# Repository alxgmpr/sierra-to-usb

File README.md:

# Sierra / Quectel 2.5GbE PoE modem appliance

Multi-gigabit WAN design study for **EM9190, EM9293, RM520N-GL and
RM551E-GL**. No CM4/CM5. **RK3566 is the selected Linux packet-processor
candidate for evaluation**, with an independent STM32 recovery MCU. The exact
modem tuples and complete appliance remain unqualified. The complete engineering
capture is in [hardware/appliance.kicad_pro](hardware/appliance.kicad_pro).

**Feasibility gate remains open.** Manufacturer documentation establishes Sierra
PCIe endpoint/USB-device operation, not modem-hosted Ethernet. A switch does not
supply the missing host and drivers. Quectel offload is a candidate requiring
exact firmware and NIC qualification. No modem combination is qualified.

- [Requirements and confirmed decisions](REQUIREMENTS.md)
- [Architecture, manufacturer evidence, networking and recovery](docs/architecture.md)
- [Historical MCU-only packet-path comparison](docs/packet-path.svg)
- [RK3566 processor qualification and current block diagram](docs/rockchip-qualification.md)
- [Block diagram and BOM qualification status](docs/qualification-status.md)
- [Power and complete-cost estimates](docs/power-and-cost.md)
- [Decoupling review and capacitor consolidation](docs/decoupling-review.md)
- [PoE stage: TPS23730 / PMP22477 evaluation (adopted)](docs/poe-tps23730-evaluation.md)
- [Reopened Rockchip Linux comparison and sourcing](docs/rockchip-options.md)
- [Actual KiCad recovery schematic](hardware/recovery.kicad_sch)
- [Implemented circuit, checks and outstanding qualification](hardware/README.md)

The full [33-sheet appliance schematic](hardware/appliance.kicad_sch) now captures
processor/RAM/eMMC, all supplies, 2.5GbE, isolated PoE, modem/SIM and recovery
interfaces: 818 components, 856 nets, **zero full ERC violations**.
[Review PDF](hardware/review/2026-10-07/appliance.pdf) and
[completion / release holds](docs/schematic-completion.md) are available.
All 818 PCB footprints are assigned, including 521 stock hand-solder variants.
Current CLI schematic/PCB parity is clean. October 7 native update-dialog
results are retained in the [footprint and model audit](docs/footprint-audit.md). Two BGA land-pattern/process
reviews, remaining model holds, current modem guides and physical/software
qualification remain open. Placement, routing and manufacturing release remain
pending.

The [October 21 BGA/model follow-up](docs/bga-model-review-2026-10-21.md)
adds six package-envelope models for 16 components (54 attached STEP assets total).
Eighteen missing-model holds and both BGA assembly-process holds remain explicit.

Previous designs remain only in Git history; none were restored for this work.

## Full schematic work — 2026-10-07

Complete appliance capture is saved in the canonical `hardware/appliance` project,
including the independent always-on supply and full recovery hierarchy. See
[completion evidence and release holds](docs/schematic-completion.md).

## Footprint and modem review — 2026-10-21

[Six-footprint review](docs/footprint-review-2026-10-21.md) closes four drawing
geometry holds and fixes TPS56837 paste/mask geometry and BGA grid rounding.
The two BGA PCB land/process holds remain. [Modem documentation gates](docs/modem-documentation.md)
record current download blockers and a PCIe-only RM520N order-code exclusion.
All four modem profiles remain unreleased. Full ERC and native parity still pass.

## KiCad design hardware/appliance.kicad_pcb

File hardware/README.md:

# Appliance schematic

The complete engineering capture is [appliance.kicad_sch](appliance.kicad_sch), with
33 sheets, 818 components and 856 native nets. Open [appliance.kicad_pro](appliance.kicad_pro)
in KiCad. [appliance.kicad_pcb](appliance.kicad_pcb) contains all 818 footprints
with native schematic links; placement and routing are still pending.

The remaining processor, boot storage, CPU power, Ethernet, isolated PoE,
modem power, M.2, SIM and USB isolation circuits are now captured. The engineering
capture passes full ERC at all severities, with **zero violations and no exclusions**.
Current CLI schematic/PCB parity is clean. The October 7 bidirectional native
update-dialog checks reported zero errors/warnings and no proposed changes. This is not a manufacturing or four-modem release.

[Review PDF](review/2026-10-07/appliance.pdf) ·
[Native BOM inventory](review/2026-10-07/bom.csv) ·
[Validation report](review/2026-10-07/capture-report.json) ·
[Footprint and model audit](../docs/footprint-audit.md) ·
[Detailed completion and release holds](../docs/schematic-completion.md)

## Reproduce and inspect

Requires KiCad CLI 10.99 (the version used for native Altium reference import) and
Python 3. Run without `python -O`; the checker uses assertions.

```sh
python3 hardware/check.py --output /tmp/sierra-appliance-check
python3 hardware/tools/check_board_sync.py --output /tmp/sierra-board-check
python3 hardware/tools/review_modem_power.py --output /tmp/modem-power-analysis.json
python3 hardware/tools/export_appliance.py --output /tmp/sierra-appliance-review
```

The checker validates the native netlist and all-severity ERC; all 565 RK3566,
200 RAM, 153 eMMC and other major-device contacts are accounted for. It checks
65 manufacturer DDR pair mappings, the complete retained TI bridge/flyback net
partitions, critical rail/reset/interface connections, four assembly-profile power
maps, deterministic identities and exact pad-number parity for all 818 assigned
footprints. Pad parity establishes identity, not a fabrication land-pattern review.
791 components use default KiCad footprints, including 521 stock hand-solder
variants. Existing package sizes are retained. All attached model paths resolve;
missing or mechanically unverified models are explicitly recorded in
[footprint-policy.json](footprint-policy.json). Imported TI embedded STEP assets
are now stored in the project.

The [BGA/model follow-up](../docs/bga-model-review-2026-10-21.md) records six new
package-envelope models covering 16 components, all 18 remaining missing-model
holds, and measured mask/stencil limits for the two unreleased BGAs. The full
checker validates model source hashes, attachment rotations and these holds;
`tools/check_model_reviews.py --geometry` additionally checks the six STEP solids
and sourced bounds with CadQuery.

The [2026-11-21 model follow-up](reference/model-reviews-2026-11-21.json) closes 11
more holds with `tools/build_models.py`: the archived Amphenol M.2 STEP attached
with a measured datum transform, the TI-embedded PowerDI-5 STEP re-oriented to its
lands, and nine envelopes (nominal XY, maximum height, drawing terminals) for U1301,
U701, U2002, U1902, U1901, U1001, L401, Y1101 and U1101. Every envelope terminal is
cross-checked against its footprint copper. Remaining holds stay in the policy.
Every generated model is a single flat, coloured STEP product with its datum transform
baked in and attaches with a zero transform, so KiCad and Backplane's 3D tab agree.

Use the native Update PCB / Update Schematic dialogs for normal edits, with
reference relinking off. `build_capture.py` regenerates the original capture and
applies the footprint policy; it overwrites manual schematic graphics. Preserve
editor changes before regeneration. `sync_board.py` is only an unrouted-board
refresh helper and refuses routed boards.

The PDF was rendered and all 30 sheets inspected. Cropped modem content, a duplicate
crystal-ground wire and the recovery USB shell-pad model were corrected during review.

## Bring-up additions — 2026-11-22

Four sheets from [tools/build_management.py](tools/build_management.py), plus native label edits on the
supervisor, processor, modem-socket, flyback, PMIC and 3.3 V sheets:

- **SoC <-> STM32 UART.** RK3566 UART3_M0 (A22 RX, B22 TX, VCCIO1 = 3V3_MAIN) to STM32 LPUART2
  (PC7 RX, PC6 TX) through two LVC1G125 buffers, each powered by its receiving side so neither
  back-powers the other. Carries telemetry, LED overrides, power-cycle requests and reset cause.
- **Status LEDs.** PWR/SYS/WAN (green) and FAULT (yellow) sink into STM32 PA8/PA15/PD0/PD1, all
  timer-PWM pins. They are dark from MCU reset until firmware drives them; Linux overrides over the UART.
- **Sensing on the STM32 ADC.** To free seven ADC inputs, seven digital signals moved to spare GPIOs
  ([assignment table](pinmaps/supervisor-appliance-assignment.csv)). PA0 AUX_12V/11, PA1 5V_MAIN/2,
  PA4 3V3_MAIN/2, PA5 MODEM_VCC/2, PA6 modem current from the TPS25947 ILM pin (R2213 must sit at U1902
  pin 9: the pin tolerates < 50 pF), PA7/PB2 10k NTCs at the M.2 bay and the flyback secondary.
  INA226 (I2C1 PB8/PB9, 0x40, alert on PC14) measures the whole 12 V bus through a 10 mOhm shunt.
- **Aux 12 V input.** J2101 (ED555) feeds ISO_12V_BUS through an LM74700 + CSD17577Q5A ideal diode; the
  flyback output (now `ISO_12V_PSU`) gets its own. `ISO_12V` is the monitored bus after the shunt.
  **Firmware:** aux power gives no PoE grant (TPH_N/TPL_N/BT_N all high). Bypass the grant gate only while
  ADC_AUX_12V reads above 10.5 V, and re-apply it as soon as aux drops. Aux is 12 V nominal, 12.6 V max.
- **Boot media.** 1.8 V SPI NOR W25Q128JWEIQ on FSPI CS0/CLK/D0/D1/D3 (D2 shares 1B16 with EMMC_RESET_N,
  so x1/x2 only); the WSON-8 8x6 land also takes W25N01GWZEIG SPI NAND. DNP microSD on SDMMC0
  (VCCIO_SD) with a TPS22965 card switch on GPIO0_A6 (SD_PWR_EN) and SDMMC0_DET card detect.
- **eSIM.** DNP MFF2 land on M.2 SIM2 contacts 42/44/46/48 through DNP 0R links, so every modem profile
  keeps those contacts open by default. The land is a placeholder pending a chosen eUICC drawing.
- **Test pads.** 80 bare 1.0 mm pads (TP2401-TP2480): 44 resets/enables/power-goods, 26 rails, 10 GND.
  PMIC_PWRON_N and MAIN3V3_EN became global nets for this. MCU_NRST_N/SWD stay on J201 and the
  service UART/modem controls on J102.

Board: placed incrementally with `place_board.py --keep` after `sync_board.py`, which now keeps existing
footprints byte-for-byte except changed pad nets. The top side had no room for 20 new parts, so they
fell back to the bottom: the aux power path and INA226 under the flyback secondary, and the SPI flash
under the SoC. J2101 is a bottom-side through-hole terminal block. The DNP microSD group is on the bottom
by design, under the M.2 card with the card opening at the right edge. DRC adds no shorts, bridges or courtyard overlaps; the six new clearance
findings are pad-to-pad inside U2103's 0.5 mm MSOP. `check_board_sync.py` still stops on six
`lib_footprint_mismatch` findings (J101, J102, J201, J202, J1202, J1701) that were already present at
the previous commit.

Open before order: SPI flash and SMBJ12CA LCSC stock; RK3566 FSPI boot behavior with a blank or
present NOR; the MFF2 land against a real eUICC drawing; microSD trace length (about 80 mm, fine for
SDR25, marginal for SDR104); the WSON-8 8x6 STEP model hold.

## PoE stage: TPS23730 / PMP22477 — 2026-11-22

The TPS2373-3 PD and the LM5155 / TL431 / opto flyback (TIDA-050023, 88 parts on two sheets) are
replaced by TI's TPS23730 PD + primary-side-regulated flyback from reference design PMP22477
(63 parts on one sheet, `poe-flyback`), per [the evaluation](../docs/poe-tps23730-evaluation.md).
[tools/build_poe_tps23730.py](tools/build_poe_tps23730.py) captures it from TI's native Altium
project (`reference/pmp22477-cad.zip`, Rev C sheet 2, imported to `reference/pmp22477-import/`).
`check_appliance_capture.py` proves the captured net partition against that import, the same way
the TIDA input bridge is still proven.

- Kept: our TIDA active input bridge (`poe-input`, option B in the evaluation, about 1 W better than
  PMP's Schottky bridge) and the three TLP293 grant optos. Grant decoding stays parallel: R65
  (SCDIS to VSS, serial mode) is left out, so firmware still enforces TPH_N/TPL_N/BT_N = 0/1/0.
  TPH/TPL optos now pull up from TPS23730 VCC (`POE_VCC`); the BT opto hangs off VB (`POE_VB`)
  through R1803 = 2.2 kOhm, because the BT pin is rated 6.5 V absolute maximum.
- Dropped from PMP sheet 2: the adapter input path (D10, L4–L6, C15, C19, C20, J10–J12), output and
  jumper terminals (J13, J14), the setpoint-shift circuit (U11, Q5, R54, R56, R57, R62), the input TVS
  D13 (D1705 on the bridge already clamps), and the whole power-limit sheet 3. The 0 Ohm straps
  R48/R49/R52/R55/R59/R60/R73 became direct ties; PPD is tied to VSS. R58 stays: it is the PSR
  feedback divider's bottom resistor, not part of the setpoint shift.
- Added: R1775, 470 Ohm 1 W preload on `ISO_12V_PSU`. The PSR output rises to about 15.7 V with no
  load (TIDT259); the preload holds about 13.4 V in standby. The `ISO_12V` normal maximum is now
  14 V (was 13.2 V); TPS54620 keeps 3.6 V margin to its 17 V limit.
- Passives use the board's standard MPNs where the spec is the same or better; the TPS23730
  (RMT0045A), LDT9055-51R transformer, FSV1060V (TO-277A) and the 47 uF can use TI's land patterns
  from the PMP22477 PCB (`PoE.pretty/TI_*`). The RMT0045A and radial-G lands have no STEP (model holds).

**Firmware:** with PSR the flyback droops with load, so with aux present the PoE share is set by the
two curves, not by the grant. Never run loads on aux while PoE is present with a grant other than
0/1/0 (PMP22477's power limiter, which handled this, is not fitted).

**Release holds:** LDT9055-51R (and its alternates Würth 750320319, Sumida PS21-212) had no
distributor stock on 2026-11-22: get a quote and samples before ordering. Confirm its isolation
rating against 802.3 / IEC 62368-1. Bench: light-load and no-load VOUT with the preload, load release
at the TPS54620 input, grant timing on a real Type 3 PSE, droop sharing with aux.

Flyback layout: `HAND` in `tools/place_board.py` holds a hand placement taken from TI's own PMP22477
Rev C board (the archived PcbDoc, imported natively), mapped onto T1702 where it already sat on the
isolation line. The primary stage keeps TI's arrangement left of the transformer, and TI's controller
cluster is turned 180° to sit above the transformer by the bridge. Distances: transformer pin 3 to the
FET drain 3.1 mm, pin 1 to the nearest input ceramic 4.5 mm, pins 6/7 to the rectifier anode 4.7 mm,
pins 9/10 to the output ceramics 4.0 mm. Every output part, C1729 included, is on top. Only the two Y
caps are on the bottom, under the transformer as in TI's layout. The always-on buck, three main
3V3/5V resistors and two test pads were moved out of the secondary area and placed again, the
buck below the flyback output. `place_board.py --keep` releases any fixed part a `HAND` entry
overlaps, and now checks a top part's through-hole pads and thermal vias against bottom parts.

## Assembly and software obligations

The default is the Quectel stuffing pattern. R2011/R2012/R2013/R2016/R2017 and
C2036/C2037/C2038 are DNP. Sierra USB profiles require all eight populated after
exact module review. Never energize Quectel contacts 24, 38 or 68. The native
[profile file](reference/modem-assembly-profiles.json) is machine-checked; all four
profiles have `released: false`. This is assembly selection, not hot interchange.

The independent STM32 must keep main, modem and NIC loads off until an isolated
Class 6 grant is stable (TPH_N/TPL_N/BT_N = 0/1/0), and cut loads on loss of grant.
It controls power, reset and recovery while Linux runs the packet path. Firmware
for those policies and real recovery/traffic behavior still need qualification.
The no-detect SIM socket permits card changes only with modem power off.

Modem USB isolation is powered from the always-on rail. Hardware enables data
only with valid host power and modem power delayed by 180–420 ms. A latched eFuse,
independent monitor and explicit discharge support recovery; measured rail fall,
USB isolation, off-time and per-model timing remain required.

## Release holds

- Two BGA PCB land/mask/paste process holds remain: U801 RK3566 and U901 Micron RAM.
  The [October 21 review](../docs/footprint-review-2026-10-21.md) closes the other four
  drawing geometry holds and records the corrected native geometry.
  Exact land patterns, copper/mask/paste, orientation and retention need review.
  RK/RAM retain the audited ball centers; connector lands follow archived vendor
  drawings. The detailed audit records mask, stencil and mechanical limitations.
- The staged board has no routing or outline. All-severity physical DRC remains
  open; the native synchronization check reports the actual counts without
  suppressing rules. Do not export it for fabrication.
- [Current modem access and order-code gates](../docs/modem-documentation.md) remain open.
  RM520N Series V1.4 is login-gated; the archived V1.0 remains provisional.
  Current controlled EM919x and EM92xx technical specifications and the RM551E-GL
  production hardware guide remain unavailable. Older manufacturer guides and the
  RM520N V1.0 guide support provisional capture. Current pin/timing differences,
  exact firmware/composition and power envelopes must be closed per module.
- 5 A modem current is a provisional burst allocation. Connector hot derating,
  voltage drop, regulator stability/current, PoE startup/MPS/allocation, thermal,
  isolation/creepage, SI/EMC and RF operation require physical testing. HV MLCCs
  across isolation are not a certified safety-barrier assembly.
- CPU DVS/kernel/DDR training/eMMC/NIC drivers and unique Ethernet MAC provisioning
  require an actual software image and boot/traffic/recovery tests.

Sources, revisions and hashes are saved in [reference/sources.json](reference/sources.json).
TI's source archives retain their notices. The active input bridge is derived from TIDA-050023 (its
golden check excludes the deleted evaluation headers, auxiliary input and old 1 GbE transformer). The
PD and flyback come from PMP22477 (below). The capture requests Class 6, extracts all four PoE pairs
with 2.5 GbE magnetics, and isolates allocation status.

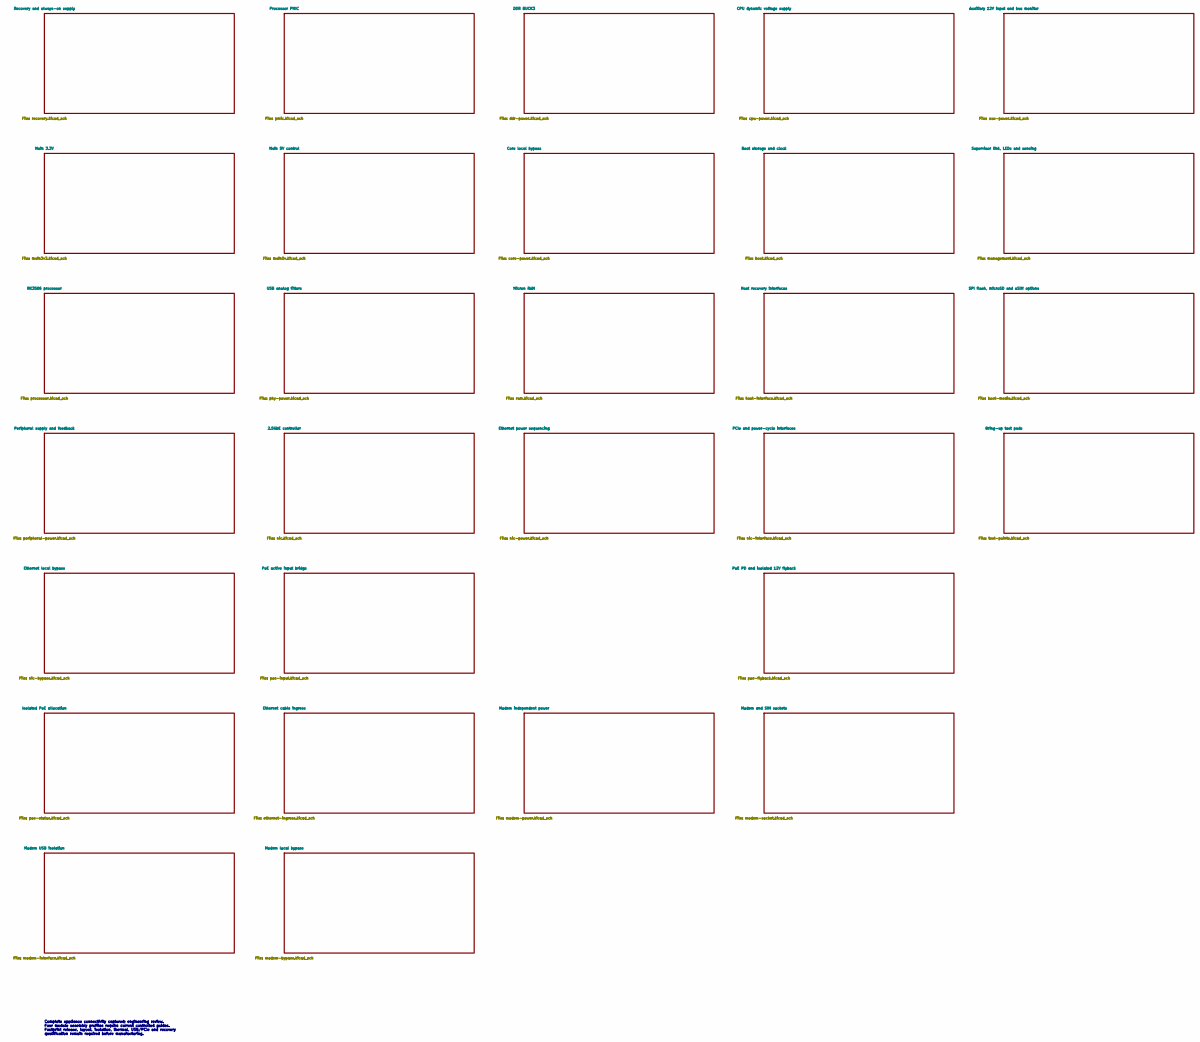
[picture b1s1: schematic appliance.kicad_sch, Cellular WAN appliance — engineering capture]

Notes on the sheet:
Complete appliance connectivity captured; engineering review. Four module assembly profiles require current controlled guides. Footprint release, layout, isolation, thermal, USB/PCIe and recovery qualification remain required before manufacturing.

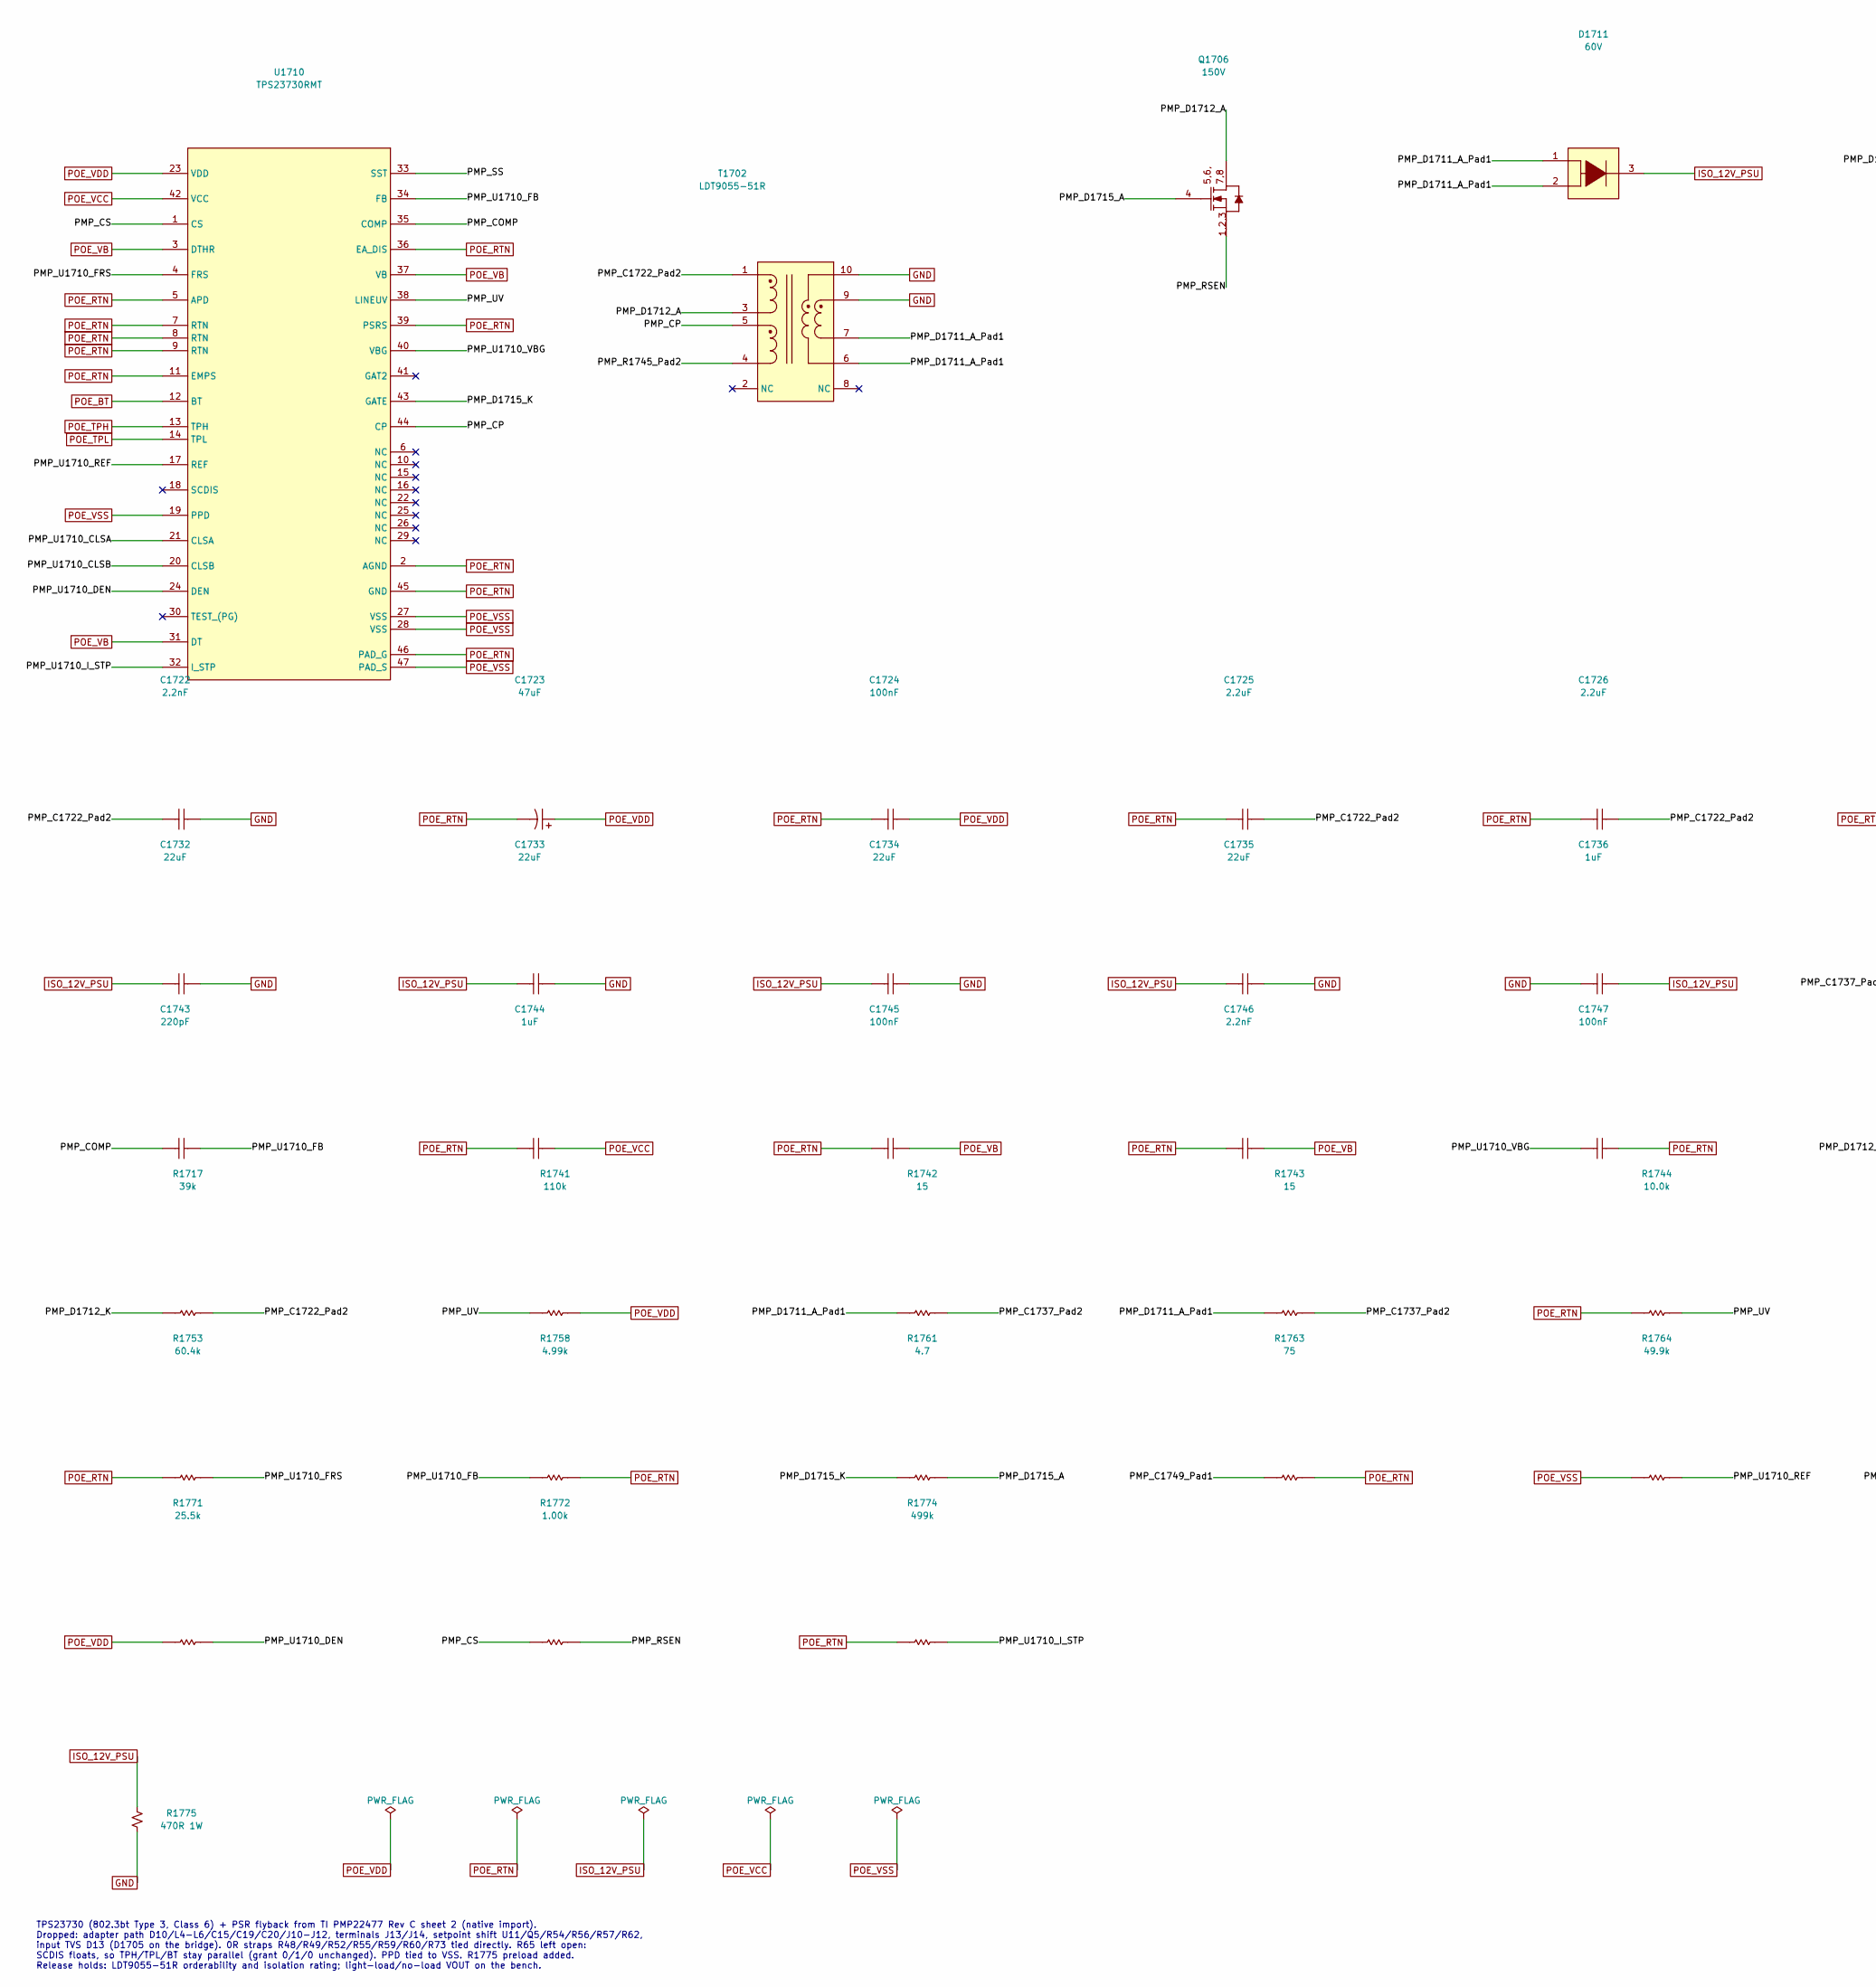
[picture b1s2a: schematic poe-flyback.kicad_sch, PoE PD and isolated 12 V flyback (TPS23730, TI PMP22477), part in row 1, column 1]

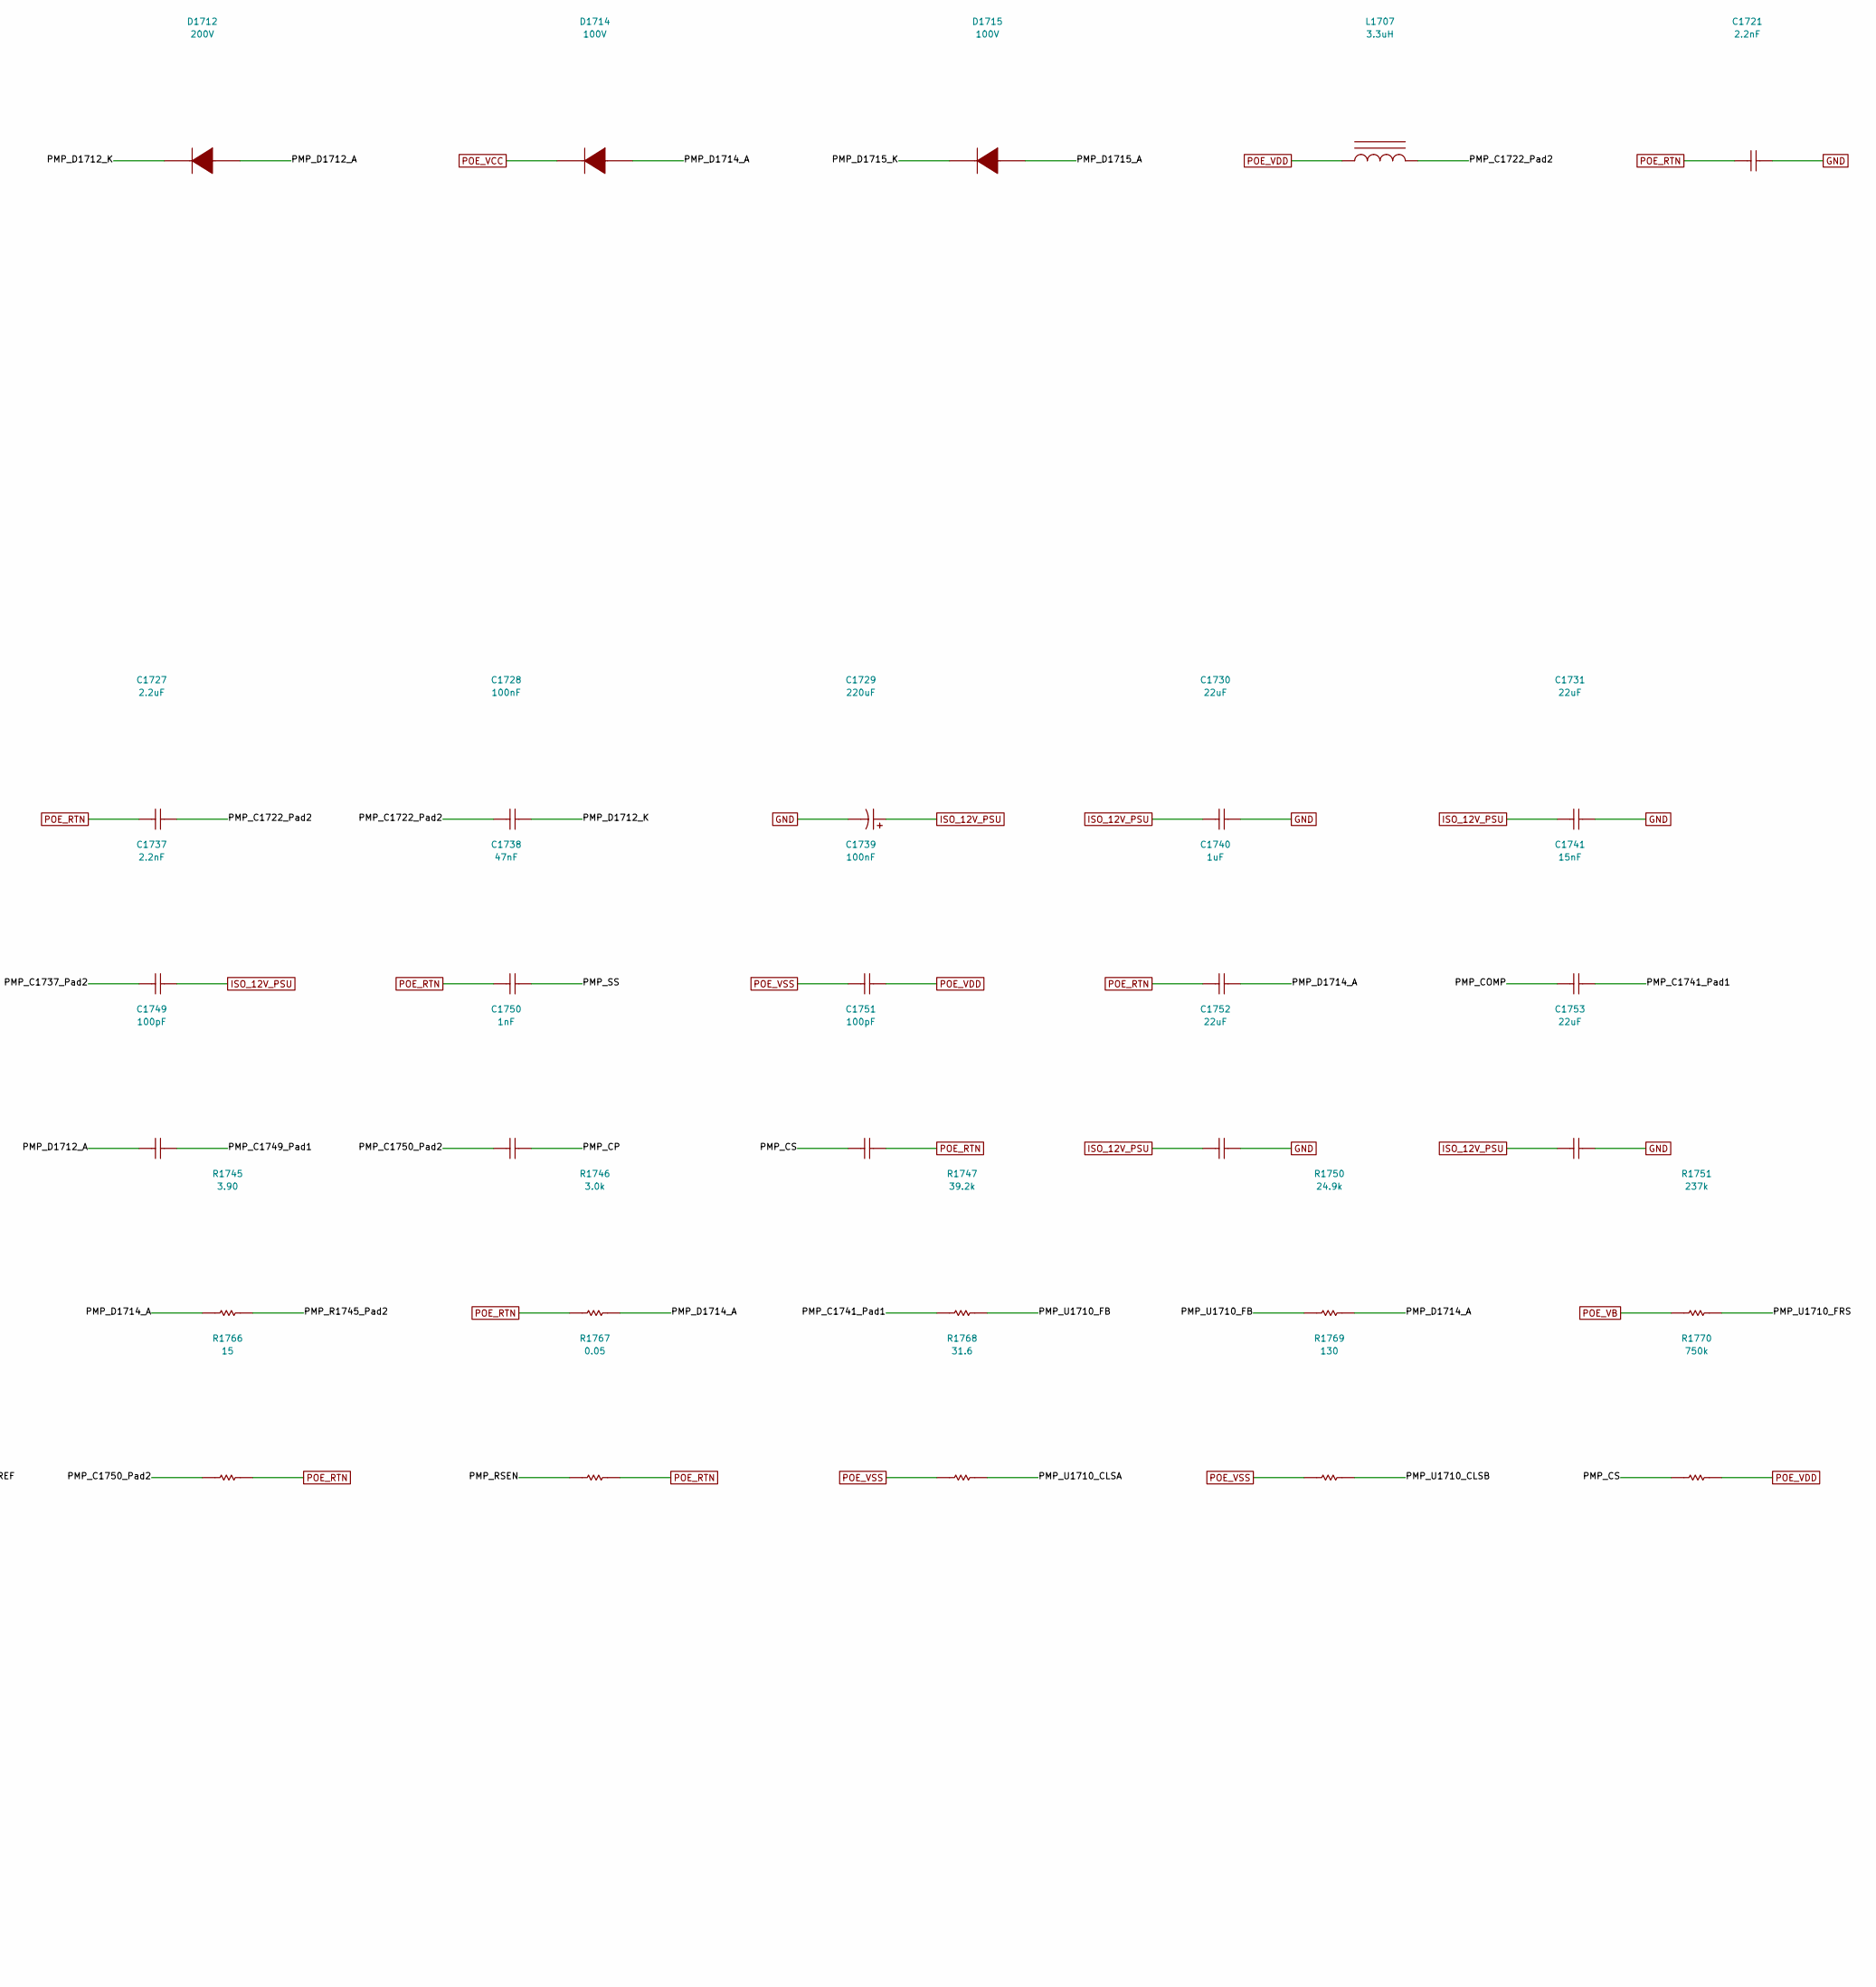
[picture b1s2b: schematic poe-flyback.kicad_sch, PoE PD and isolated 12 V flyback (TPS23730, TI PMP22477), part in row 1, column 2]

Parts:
C1721, C1722: 2.2nF; C_1812_4532Metric_Pad1.57x3.40mm_HandSolder; Voltage Rating 2kV; Tolerance 10%; MPN C4532X7R3D222K130KA
C1723: 47uF; CP_Elec_10x10.5; Voltage Rating 80V; Tolerance 20%; MPN EEE-FK1K470P
C1724, C1728, C1739: 100nF; C_0805_2012Metric_Pad1.18x1.45mm_HandSolder; Voltage Rating 100V; Tolerance 10%; MPN C2012X7R2A104K125AA
C1725, C1726, C1727: 2.2uF; C_1210_3225Metric_Pad1.33x2.70mm_HandSolder; Voltage Rating 100V; Tolerance 10%; MPN GRM32ER72A225KA35L
C1729: 220uF; CP_Elec_8x10.5; Voltage Rating 25V; Tolerance 20%; MPN EEE-FK1E221P
C1730, C1731, C1732, C1733, C1734, C1735, C1752, C1753: 22uF; C_1210_3225Metric_Pad1.33x2.70mm_HandSolder; Voltage Rating 25V; Tolerance 10%; MPN CL32B226KAJNNNE
C1736, C1740, C1744: 1uF; C_0603_1608Metric_Pad1.08x0.95mm_HandSolder; Voltage Rating 25V; Tolerance 10%; MPN CL10B105KA8NNNC
C1737, C1746: 2.2nF; C_0603_1608Metric_Pad1.08x0.95mm_HandSolder; Voltage Rating 100V; Tolerance 10%; MPN 06031C222KAT2A
C1738: 47nF; C_0603_1608Metric_Pad1.08x0.95mm_HandSolder; Voltage Rating 50V; Tolerance 10%; MPN CL10B473KB8NNNC
C1741: 15nF; C_0603_1608Metric_Pad1.08x0.95mm_HandSolder; Voltage Rating 50V; Tolerance 10%; MPN C1608X7R1H153K080AA
C1743: 220pF; C_0603_1608Metric_Pad1.08x0.95mm_HandSolder; Voltage Rating 50V; Tolerance 5%; MPN CL10C221JB8NNNC
C1745, C1747: 100nF; C_0603_1608Metric_Pad1.08x0.95mm_HandSolder; Voltage Rating 25V; Tolerance 10%; MPN CL10B104KA8NNNC
C1749: 100pF; C_0805_2012Metric_Pad1.18x1.45mm_HandSolder; Voltage Rating 250V; Tolerance 5%; MPN GRM21A5C2E101JW01D
C1750: 1nF; C_0603_1608Metric_Pad1.08x0.95mm_HandSolder; Voltage Rating 100V; Tolerance 10%; MPN C1608X7R2A102K
C1751: 100pF; C_0603_1608Metric_Pad1.08x0.95mm_HandSolder; Voltage Rating 50V; Tolerance 5%; MPN CL10C101JB8NNNC
D1711: 60V; TI_TO-277A; MPN FSV1060V
D1712: 200V; D_SMA_Handsoldering; MPN ES1D-13-F
D1714, D1715: 100V; D_SOD-123; MPN MMSD4148T1G
L1707: 3.3uH; L_Coilcraft_LPS4018; MPN LPS4018-332MLB
Q1706: 150V; TI_TRANS_Fairchild_PQFN08A; MPN FDMS86252
R1717: 39k; R_1206_3216Metric_Pad1.30x1.75mm_HandSolder; Tolerance 5%; Power Rating 250mW; MPN CRCW120639K0JNEA
R1741: 110k; R_0603_1608Metric_Pad0.98x0.95mm_HandSolder; Tolerance 1%; Power Rating 100mW; MPN RC0603FR-07110KL
R1742, R1743: 15; R_2512_6332Metric_Pad1.40x3.35mm_HandSolder; Tolerance 5%; Power Rating 1W; MPN CRCW251215R0JNEG
R1744: 10.0k; R_0603_1608Metric_Pad0.98x0.95mm_HandSolder; Tolerance 1%; Power Rating 100mW; MPN RC0603FR-0710KL
R1745: 3.90; R_0805_2012Metric_Pad1.20x1.40mm_HandSolder; Tolerance 1%; Power Rating 125mW; MPN ERJ-6RQF3R9V
R1746: 3.0k; R_1206_3216Metric_Pad1.30x1.75mm_HandSolder; Tolerance 5%; Power Rating 250mW; MPN CRCW12063K00JNEA
R1747: 39.2k; R_0603_1608Metric_Pad0.98x0.95mm_HandSolder; Tolerance 1%; Power Rating 100mW; MPN RC0603FR-0739K2L
R1750: 24.9k; R_0603_1608Metric_Pad0.98x0.95mm_HandSolder; Tolerance 1%; Power Rating 100mW; MPN RC0603FR-0724K9L
R1751: 237k; R_0603_1608Metric_Pad0.98x0.95mm_HandSolder; Tolerance 1%; Power Rating 100mW; MPN RC0603FR-07237KL
R1753: 60.4k; R_0603_1608Metric_Pad0.98x0.95mm_HandSolder; Tolerance 1%; Power Rating 100mW; MPN RC0603FR-0760K4L
R1758: 4.99k; R_0603_1608Metric_Pad0.98x0.95mm_HandSolder; Tolerance 1%; Power Rating 100mW; MPN RC0603FR-074K99L
R1761: 4.7; R_0603_1608Metric_Pad0.98x0.95mm_HandSolder; Tolerance 5%; Power Rating 100mW; MPN RC0603FR-074R7L
R1763: 75; R_2010_5025Metric_Pad1.40x2.65mm_HandSolder; Tolerance 5%; Power Rating 750mW; MPN CRCW201075R0JNEF
R1764: 49.9k; R_0603_1608Metric_Pad0.98x0.95mm_HandSolder; Tolerance 1%; Power Rating 100mW; MPN RC0603FR-0749K9L
R1766: 15; R_1206_3216Metric_Pad1.30x1.75mm_HandSolder; Tolerance 5%; Power Rating 250mW; MPN CRCW120615R0JNEA
R1767: 0.05; R_2010_5025Metric_Pad1.40x2.65mm_HandSolder; Tolerance 1%; Power Rating 1W; MPN CSRN2010FK50L0
R1768: 31.6; R_0805_2012Metric_Pad1.20x1.40mm_HandSolder; Tolerance 1%; Power Rating 125mW; MPN CRCW080531R6FKEA
R1769: 130; R_0805_2012Metric_Pad1.20x1.40mm_HandSolder; Tolerance 1%; Power Rating 125mW; MPN CRCW0805130RFKEA
R1770: 750k; R_0603_1608Metric_Pad0.98x0.95mm_HandSolder; Tolerance 5%; Power Rating 100mW; MPN RC0603FR-07750KL
R1771: 25.5k; R_0603_1608Metric_Pad0.98x0.95mm_HandSolder; Tolerance 1%; Power Rating 100mW; MPN RC0603FR-0725K5L
R1772: 1.00k; R_0603_1608Metric_Pad0.98x0.95mm_HandSolder; Tolerance 1%; Power Rating 100mW; MPN RC0603FR-071KL
R1774: 499k; R_0603_1608Metric_Pad0.98x0.95mm_HandSolder; Tolerance 1%; Power Rating 100mW; MPN RC0603FR-07499KL
R1775: 470R 1W; R_2512_6332Metric_Pad1.40x3.35mm_HandSolder; Tolerance 1%; Power Rating 1W; MPN RC2512FK-07470RL
T1702: LDT9055-51R; TI_LDT9055; MPN LDT9055-51R
U1710: TPS23730RMT; TI_RMT0045A; MPN TPS23730RMT

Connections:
/PoE PD and isolated 12V flyback/PMP_C1722_Pad2: C1722.2, C1725.1, C1726.1, C1727.1, C1728.2, L1707.2, R1717.2, T1702.1
/PoE PD and isolated 12V flyback/PMP_C1737_Pad2: C1737.2, R1742.2, R1743.2
/PoE PD and isolated 12V flyback/PMP_C1741_Pad1: C1741.1, R1747.1
/PoE PD and isolated 12V flyback/PMP_C1749_Pad1: C1749.1, R1763.1
/PoE PD and isolated 12V flyback/PMP_C1750_Pad2: C1750.2, R1766.1
/PoE PD and isolated 12V flyback/PMP_COMP: C1741.2, C1743.2, U1710.35 (COMP)
/PoE PD and isolated 12V flyback/PMP_CP: C1750.1, T1702.5, U1710.44 (CP)
/PoE PD and isolated 12V flyback/PMP_CS: C1751.2, R1770.1, R1772.1, U1710.1 (CS)
/PoE PD and isolated 12V flyback/PMP_D1711_A_Pad1: D1711.1 (A), D1711.2 (A), R1742.1, R1743.1, T1702.6, T1702.7
/PoE PD and isolated 12V flyback/PMP_D1712_A: C1749.2, D1712.2 (A), Q1706.5 (D), Q1706.6 (D), Q1706.7 (D), Q1706.8 (D), T1702.3
/PoE PD and isolated 12V flyback/PMP_D1712_K: C1728.1, D1712.1 (K), R1717.1
/PoE PD and isolated 12V flyback/PMP_D1714_A: C1740.1, D1714.2 (A), R1745.1, R1746.2, R1750.2
/PoE PD and isolated 12V flyback/PMP_D1715_A: D1715.2 (A), Q1706.4 (G), R1761.2
/PoE PD and isolated 12V flyback/PMP_D1715_K: D1715.1 (K), R1761.1, U1710.43 (GATE)
/PoE PD and isolated 12V flyback/PMP_R1745_Pad2: R1745.2, T1702.4
/PoE PD and isolated 12V flyback/PMP_RSEN: Q1706.1 (S), Q1706.2 (S), Q1706.3 (S), R1767.1, R1772.2
/PoE PD and isolated 12V flyback/PMP_SS: C1738.1, U1710.33 (SST)
/PoE PD and isolated 12V flyback/PMP_U1710_CLSA: R1768.2, U1710.21 (CLSA)
/PoE PD and isolated 12V flyback/PMP_U1710_CLSB: R1769.2, U1710.20 (CLSB)
/PoE PD and isolated 12V flyback/PMP_U1710_DEN: R1771.2, U1710.24 (DEN)
/PoE PD and isolated 12V flyback/PMP_U1710_FB: C1743.1, R1747.2, R1750.1, R1758.1, U1710.34 (FB)
/PoE PD and isolated 12V flyback/PMP_U1710_FRS: R1751.2, R1753.2, U1710.4 (FRS)
/PoE PD and isolated 12V flyback/PMP_U1710_I_STP: R1774.2, U1710.32 (I_STP)
/PoE PD and isolated 12V flyback/PMP_U1710_REF: R1764.2, U1710.17 (REF)
/PoE PD and isolated 12V flyback/PMP_U1710_VBG: C1747.2, U1710.40 (VBG)
/PoE PD and isolated 12V flyback/PMP_UV: R1741.1, R1744.2, U1710.38 (LINEUV)
GND: C1721.1, C1722.1, C1729.2 (-), C1730.1, C1731.1, C1732.1, C1733.1, C1734.1, C1735.1, C1736.2, C1752.1, C1753.1, R1775.2, T1702.9, T1702.10; also elsewhere on the board
ISO_12V_PSU: C1729.1 (+), C1730.2, C1731.2, C1732.2, C1733.2, C1734.2, C1735.2, C1736.1, C1737.1, C1752.2, C1753.2, D1711.3 (K), R1775.1; also elsewhere on the board
POE_BT: U1710.12 (BT); also elsewhere on the board
POE_RTN: C1721.2, C1723.2 (-), C1724.2, C1725.2, C1726.2, C1727.2, C1738.2, C1740.2, C1744.2, C1745.2, C1746.2, C1747.1, C1751.1, R1744.1, R1746.1, R1753.1, R1758.2, R1763.2, R1766.2, R1767.2, R1774.1, U1710.2 (AGND), U1710.5 (APD), U1710.7 (RTN), U1710.8 (RTN), U1710.9 (RTN), U1710.11 (EMPS), U1710.36 (EA_DIS), U1710.39 (PSRS), U1710.45 (GND), U1710.46 (PAD_G)
POE_TPH: U1710.13 (TPH); also elsewhere on the board
POE_TPL: U1710.14 (TPL); also elsewhere on the board
POE_VB: C1745.1, C1746.1, R1751.1, U1710.3 (DTHR), U1710.31 (DT), U1710.37 (VB); also elsewhere on the board
POE_VCC: C1744.1, D1714.1 (K), U1710.42 (VCC); also elsewhere on the board
POE_VDD: C1723.1 (+), C1724.1, C1739.1, L1707.1, R1741.2, R1770.2, R1771.1, U1710.23 (VDD); also elsewhere on the board
POE_VSS: C1739.2, R1764.1, R1768.1, R1769.1, U1710.19 (PPD), U1710.27 (VSS), U1710.28 (VSS), U1710.47 (PAD_S); also elsewhere on the board

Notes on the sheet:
TPS23730 (802.3bt Type 3, Class 6) + PSR flyback from TI PMP22477 Rev C sheet 2 (native import). Dropped: adapter path D10/L4-L6/C15/C19/C20/J10-J12, terminals J13/J14, setpoint shift U11/Q5/R54/R56/R57/R62, input TVS D13 (D1705 on the bridge). 0R straps R48/R49/R52/R55/R59/R60/R73 tied directly. R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
